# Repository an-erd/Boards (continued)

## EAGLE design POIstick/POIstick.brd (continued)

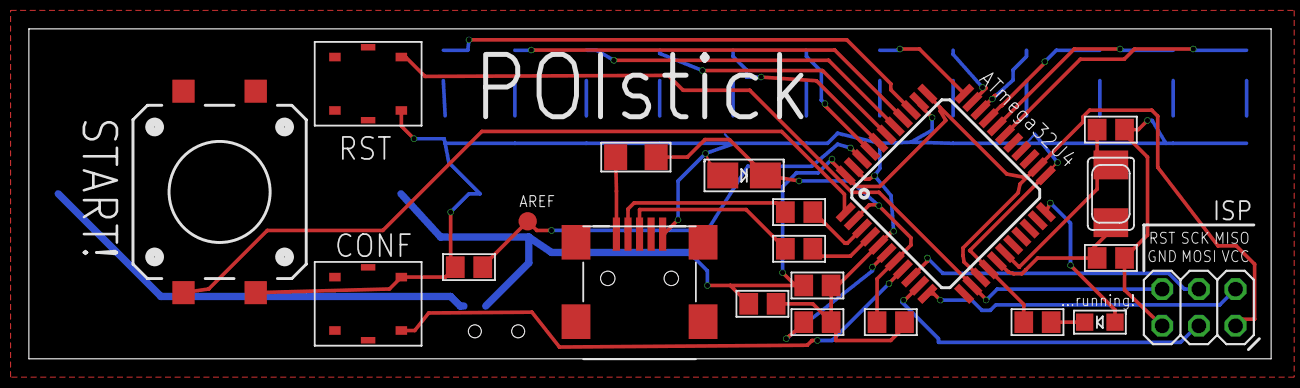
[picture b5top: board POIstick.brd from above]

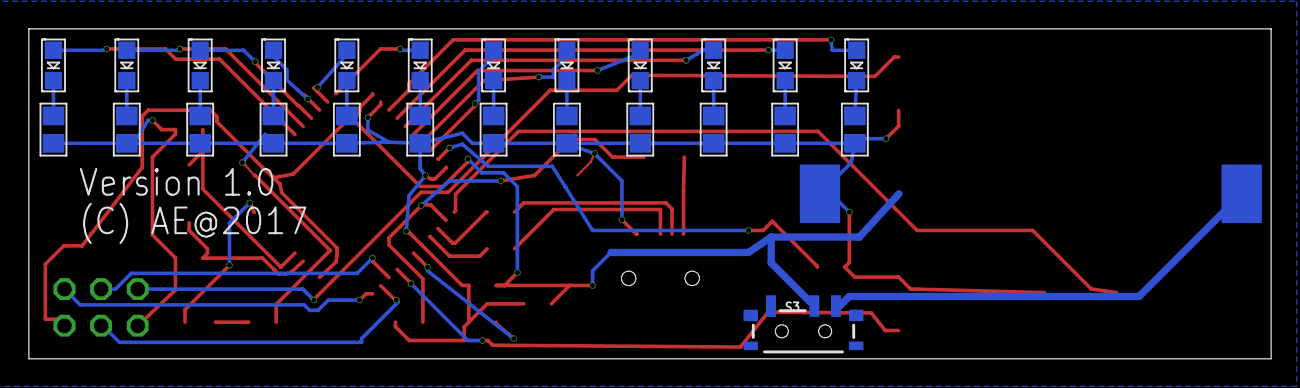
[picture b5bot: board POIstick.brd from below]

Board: 2 copper layers, 86.0 x 22.9 mm, 47 parts (26 on the bottom side), 45 nets.

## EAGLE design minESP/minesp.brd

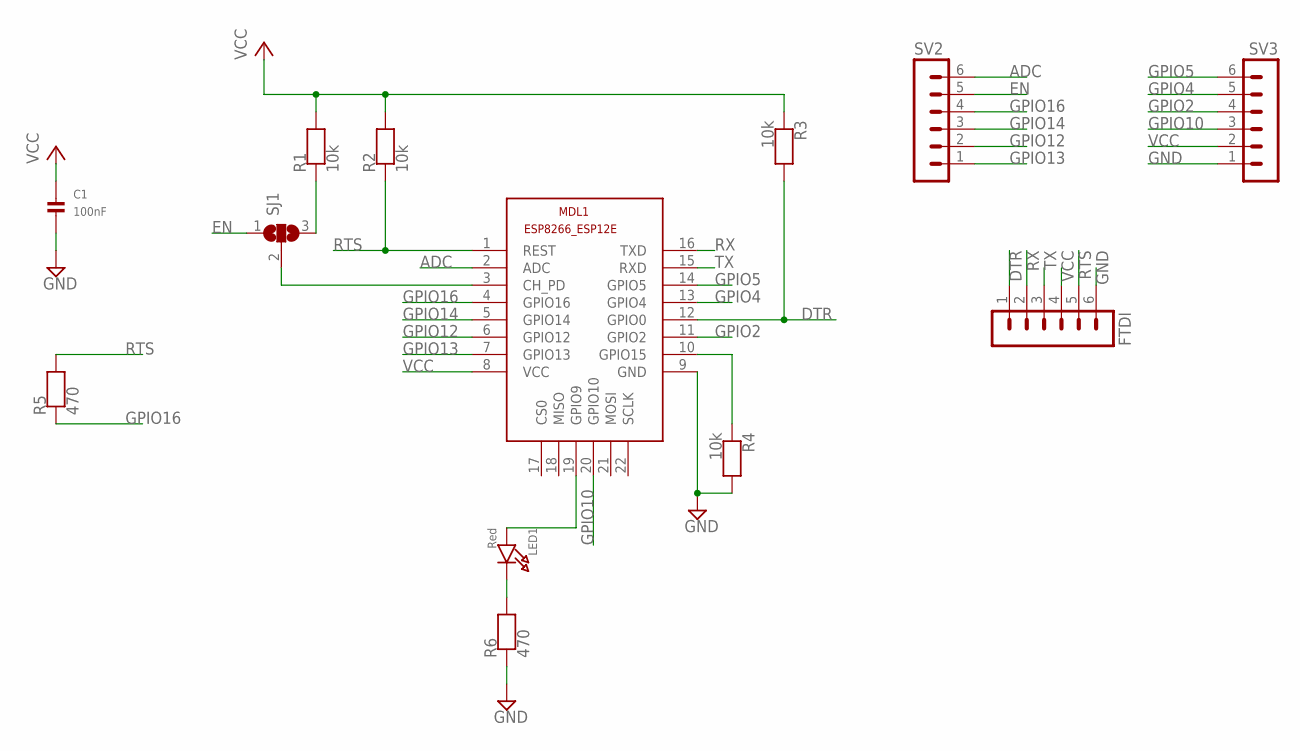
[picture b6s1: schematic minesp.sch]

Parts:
C1: 100nF; 0805
FTDI: MA06-1
LED1: Red; CHIPLED_0805
MDL1: ESP8266-12EESP8266-ESP12E; ESP8266-ESP12E
R1, R2, R3, R4: 10k; 0805
R5, R6: 470; 0805
SJ1: SJ2W; SJ_2
SV2, SV3: MA06-1

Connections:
ADC: MDL1.2 (ADC), SV2.6
DTR: FTDI.1, MDL1.12 (GPIO0), R3.2
EN: SJ1.1, SV2.5
GND: C1.2, FTDI.6, MDL1.9 (GND), R4.2, R6.1, SV3.1
GPIO2: MDL1.11 (GPIO2), SV3.4
GPIO4: MDL1.13 (GPIO4), SV3.5
GPIO5: MDL1.14 (GPIO5), SV3.6
GPIO10: MDL1.20 (GPIO10), SV3.3
GPIO12: MDL1.6 (GPIO12), SV2.2
GPIO13: MDL1.7 (GPIO13), SV2.1
GPIO14: MDL1.5 (GPIO14), SV2.3
GPIO16: MDL1.4 (GPIO16), R5.1, SV2.4
unnamed: LED1.A, MDL1.19 (GPIO9)
unnamed: MDL1.3 (CH_PD), SJ1.2
unnamed: LED1.C, R6.2
unnamed: MDL1.10 (GPIO15), R4.1
unnamed: R1.1, SJ1.3
RTS: FTDI.5, MDL1.1 (REST), R2.1, R5.2
RX: FTDI.2, MDL1.16 (TXD)
TX: FTDI.3, MDL1.15 (RXD)
VCC: C1.1, FTDI.4, MDL1.8 (VCC), R1.2, R2.2, R3.1, SV3.2

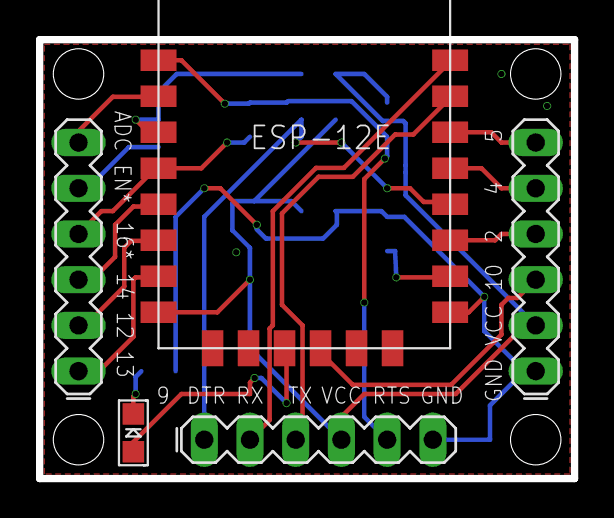
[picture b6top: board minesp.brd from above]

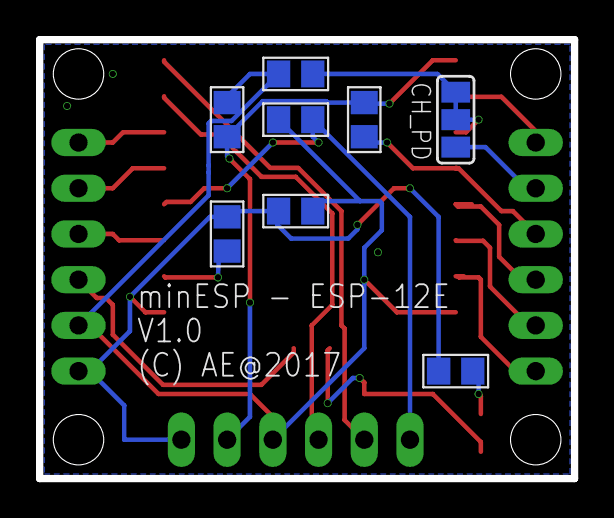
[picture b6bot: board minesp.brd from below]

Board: 2 copper layers, 29.7 x 24.4 mm, 13 parts (8 on the bottom side), 21 nets.

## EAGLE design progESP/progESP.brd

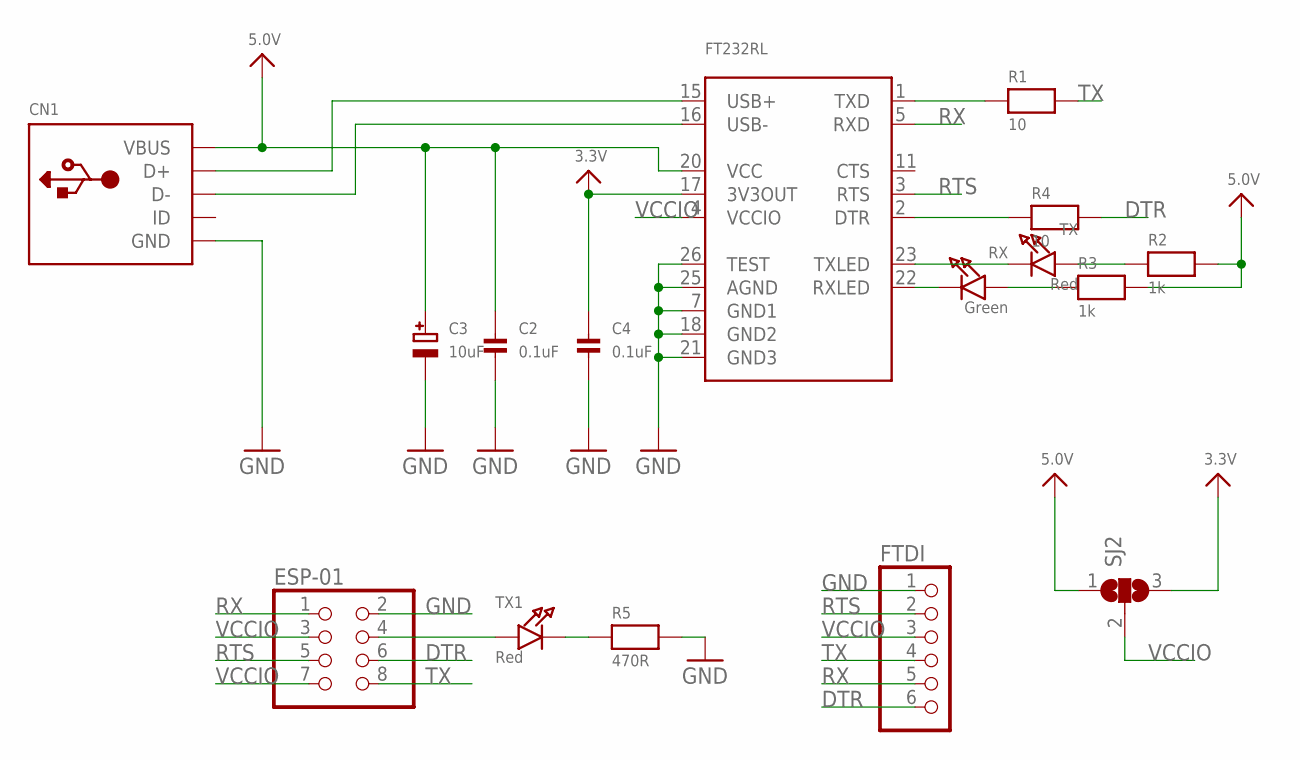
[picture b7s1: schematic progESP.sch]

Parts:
C2, C4: 0.1uF; 0805
C3: 10uF; EIA3216-18/A-R
CN1: USBMINIB; USB-MINIB
ESP-01: PINHD-2X4-ESP-01; 2X04
FT232RL: FT232RLSSOP28; SSOP28DB
FTDI: PINHD-1X6; 1X06
R1, R4: 10; 0805
R2, R3: 1k; 0805
R5: 470R; 0805
RX: Green; CHIPLED_0805
SJ2: SJ2W; SJ_2
TX, TX1: Red; CHIPLED_0805

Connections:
3.3V: C4.1, FT232RL.17 (3V3OUT), SJ2.3
5.0V: C2.1, C3.+, CN1.VBUS, FT232RL.20 (VCC), R2.2, R3.2, SJ2.1
DTR: ESP-01.6, FTDI.6, R4.2
GND: C2.2, C3.-, C4.2, CN1.GND, ESP-01.2, FT232RL.7 (GND1), FT232RL.18 (GND2), FT232RL.21 (GND3), FT232RL.25 (AGND), FT232RL.26 (TEST), FTDI.1, R5.2
unnamed: FT232RL.2 (DTR), R4.1
unnamed: CN1.D+, FT232RL.15 (USB+)
unnamed: CN1.D-, FT232RL.16 (USB-)
unnamed: FT232RL.23 (TXLED), TX.C
unnamed: FT232RL.1 (TXD), R1.1
unnamed: FT232RL.22 (RXLED), RX.C
unnamed: R3.1, RX.A
unnamed: R2.1, TX.A
unnamed: ESP-01.4, TX1.A
unnamed: R5.1, TX1.C
RTS: ESP-01.5, FT232RL.3 (RTS), FTDI.2
RX: ESP-01.1, FT232RL.5 (RXD), FTDI.5
TX: ESP-01.8, FTDI.4, R1.2
VCCIO: ESP-01.3, ESP-01.7, FT232RL.4 (VCCIO), FTDI.3, SJ2.2

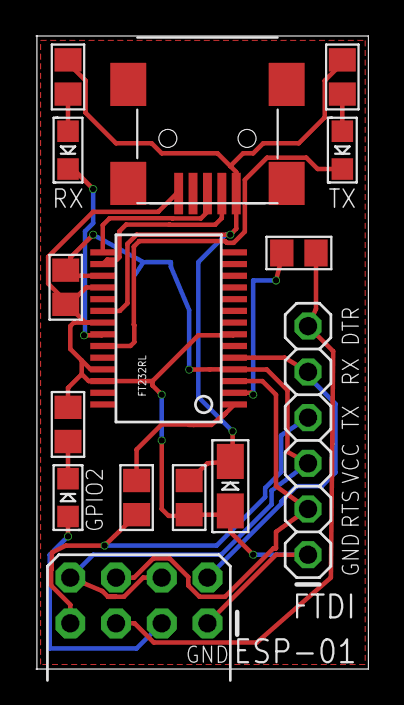
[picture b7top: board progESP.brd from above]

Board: 2 copper layers, 18.4 x 35.2 mm, 16 parts (1 on the bottom side), 18 nets.

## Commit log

2017-09-18 initial checkin
2017-09-19 Rev 2
2017-09-19 POIstick Rev 3
2017-09-19 POIstick Rev 7
2017-10-10 UCAP 0.1uF, replace 3.3V -> VCC
2017-10-10 update WIP
2017-10-10 update init checkin TR and Stethi
2017-10-10 Initial legoPFremote commit
2017-10-23 initial V2
